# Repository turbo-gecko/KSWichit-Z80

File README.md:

# KS Wichit Z80 Microprocessor Kit

The KS Wichit Z80 Microprocessor Kit is a modern retro re-imagining of the MPF-1 microprocessor trainer. The home page for the Z80 kit is https://kswichit.net/Z80/Z80.html

After expanding my original MPF-1, I figured I could do the same for the Z80 kit. I would use the same/similar expansion bus and cards as the MPF-1, but would need a specialised adapter to connect to the Z80 kit.

This repo is for the hardware and software I have developed for the Z80 kit to expand and improve the Z80 kits useability.

## How to expand the Z80 Kit
The following section descibes how to expand the capabilities of the Z80 kit to make use conveniences like fast serial download, SD card storage etc.

The expansion bus of choice that works very well with the Z80 kit is the retro modern RCBus by Small Computer Central, and the RC2014 bus. 2 adapter cards are required to connect the Z80 kit to the expansion bus.
- Z80 kit to Z80 bus adapter. https://github.com/turbo-gecko/KSWichit-Z80/tree/main/Hardware/Z80%20Bus%20Adapter
- Z80 bus to RC2014 adapter. https://github.com/turbo-gecko/MPF/tree/main/Hardware/Z80%20Bus%20to%20RCBus

### Basic expansion bus
A basic expansion bus will require as a minimum:
- RCBus/RC2014 backplane. The one in the photo is an SC147 https://smallcomputercentral.com/sc147-modular-backplane-rc2014/
- A power supply for the backplane. The one in the photo is an SC142 that has been modified to switch the incoming 9VDC to the Z80 kit. This allows a single switch to power on/off the complete system. https://smallcomputercentral.com/sc142-power-module-rc2014/
- 40 pin ribbon cable to connect the Z80 kit to the backplane via the adapter.

This provides the necessary backplane, power and connectivity to expand the Z80 kit.

### Adding additional memory
The Z80 kit comes with 32K of RAM fitted from 1000H to 8FFFH. This is a useful amount of memory however it can be expanded to a full 60K of RAM, from 1000H to FFFFH.

First is to modify the 16V8 PAL chip to reduce the existing 32K of RAM back to 28K to allow for the second additional memory bank. The changes are included at https://github.com/turbo-gecko/KSWichit-Z80/tree/main/Hardware/16V8%20PAL

Second is a memory expansion card with 32K of RAM such as:
- The 32K RAM, standard bus version of the module at https://z80kits.com/shop/64k-ram-module/ is a good choice. This is the module that is fitted in the backplane in the photo's. It has been configured to provide RAM from 8000H through to FFFFH.

### High speed serial
The expansion bus allows a high speed serial card to be added and along with a hex download program. This enables much faster downloading of hex files to the Z80 kit compared to the onboard bit-banged serial port. The serial card in the photo's is an ACIA single serial card. https://smallcomputercentral.com/sc139-serial-68b50-module-rc2014/

### SD card storage
To store and load files using an SD card only requires an I/O card and an Adafruit style SD card adapter. The I/O card in the photo is an SC129 https://smallcomputercentral.com/sc129-digital-i-o-rc2014/.

### Optional ROM upgrade
This is an optional step to enable the faster hex file downloading from within the ROM. It is not required, as the onbaord hex loader can be used.

The ROMs at https://github.com/turbo-gecko/KSWichit-Z80/tree/main/Hardware/ROM contain the hex-load program at 0DD0H that uses the high speed serial card.

Burn the binary image to a 27C256 EPROM and replace the existing ROM the Z80 kit.

### Configuration

#### Serial
The software has been designed to work with an ACIA serial card only (more in the works) at I/O address C8H. The hex load and SD card programs are designed to use the serial card at 115kbps with RTS/CTS handshaking. There is further information on the serial card at https://github.com/turbo-gecko/MPF/tree/main/Software/Hex%20Load

#### SD Card
The I/O card should be configured to use address FDH, however this can be modified along with the pin configurations in the spi_IO.ASM file at https://github.com/turbo-gecko/MPF/tree/main/Software/Library.

Default pin configurations as follows:
| I/O | Pin | Description |
| --- | --- | ----------- |
| In  |  7  | MISO        |
| Out |  0  | MOSI        |
| Out |  1  | CLK         |
| Out |  2  | CS          |

Make sure that the SD card module is designed to run off 5VDC and has the 3V3 reg on board to drive the SD card correctly.

### Using the expansion cards
Once you have everything up and running, you can try using the hex load program at 0DD0H (if the optional ROM upgrade is done) or by pressing the 'LOAD' button to download the 'Port LED Walk' example (Port LED Walk.hex) from https://github.com/turbo-gecko/KSWichit-Z80/tree/main/Software/Examples. Download the hex file and run the program at 1800H.

### Troubleshooting
- Start with the backplane, power supply and ribbon cable first. Make sure that when both the backplane and the Z80 kit is powered on, the Z80 kit works as normal.
- Power off the system, add the expansion cards one at a time, power back on and confirm the Z80 kit is working. If it isn't check
  - The ribbon cable is connected correctly. See photo for details.
  - The expansion card is seated correctly in the backplane.

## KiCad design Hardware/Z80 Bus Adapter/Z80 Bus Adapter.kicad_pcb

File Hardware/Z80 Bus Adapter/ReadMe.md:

# Z80 Bus Adapter

Here are the files for the PCB to modify the Z80 kit expansion bus to the standard Z80 bus. The 'plots' folder contains the zip file of the grebers for a PCB manufacturer house such as JLCPCB.

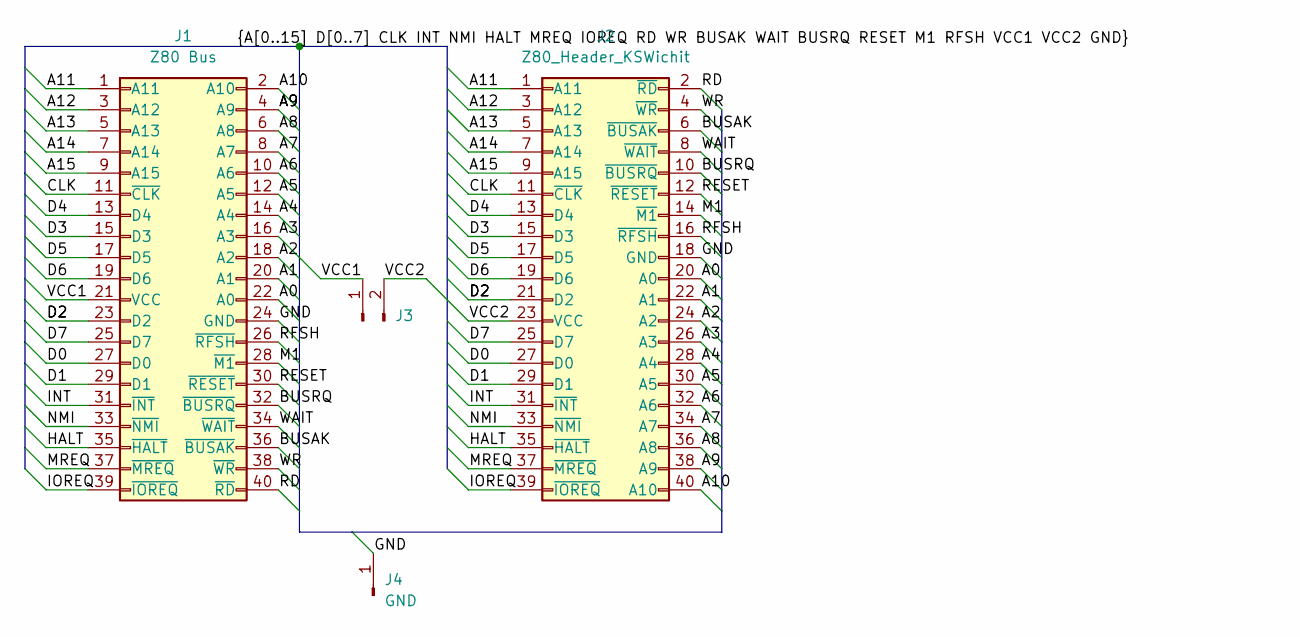
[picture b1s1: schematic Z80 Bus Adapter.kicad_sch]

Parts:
J1: Z80 Bus; PinSocket_2x20_P2.54mm_Vertical
J2: Z80_Header_KSWichit; PinSocket_2x20_P2.54mm_Vertical
J3: Conn_01x02_Pin; PinHeader_1x02_P2.54mm_Vertical
J4: GND; PinHeader_1x01_P2.54mm_Vertical

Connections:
/A0: J1.22 (A0), J2.20 (A0)
/A1: J1.20 (A1), J2.22 (A1)
/A2: J1.18 (A2), J2.24 (A2)
/A3: J1.16 (A3), J2.26 (A3)
/A4: J1.14 (A4), J2.28 (A4)
/A5: J1.12 (A5), J2.30 (A5)
/A6: J1.10 (A6), J2.32 (A6)
/A7: J1.8 (A7), J2.34 (A7)
/A8: J1.6 (A8), J2.36 (A8)
/A9: J1.4 (A9), J2.38 (A9)
/A10: J1.2 (A10), J2.40 (A10)
/A11: J1.1 (A11), J2.1 (A11)
/A12: J1.3 (A12), J2.3 (A12)
/A13: J1.5 (A13), J2.5 (A13)
/A14: J1.7 (A14), J2.7 (A14)
/A15: J1.9 (A15), J2.9 (A15)
/BUSAK: J1.36 (~BUSAK), J2.6 (~BUSAK)
/BUSRQ: J1.32 (~BUSRQ), J2.10 (~BUSRQ)
/CLK: J1.11 (~CLK), J2.11 (~CLK)
/D0: J1.27 (D0), J2.27 (D0)
/D1: J1.29 (D1), J2.29 (D1)
/D2: J1.23 (D2), J2.21 (D2)
/D3: J1.15 (D3), J2.15 (D3)
/D4: J1.13 (D4), J2.13 (D4)
/D5: J1.17 (D5), J2.17 (D5)
/D6: J1.19 (D6), J2.19 (D6)
/D7: J1.25 (D7), J2.25 (D7)
/GND: J1.24 (GND), J2.18 (GND), J4.1
/HALT: J1.35 (~HALT), J2.35 (~HALT)
/INT: J1.31 (~INT), J2.31 (~INT)
/IOREQ: J1.39 (~IOREQ), J2.39 (~IOREQ)
/M1: J1.28 (~M1), J2.14 (~M1)
/MREQ: J1.37 (~MREQ), J2.37 (~MREQ)
/NMI: J1.33 (~NMI), J2.33 (~NMI)
/RD: J1.40 (~RD), J2.2 (~RD)
/RESET: J1.30 (~RESET), J2.12 (~RESET)
/RFSH: J1.26 (~RFSH), J2.16 (~RFSH)
/VCC1: J1.21 (VCC), J3.1
/VCC2: J2.23 (VCC), J3.2
/WAIT: J1.34 (~WAIT), J2.8 (~WAIT)
/WR: J1.38 (~WR), J2.4 (~WR)

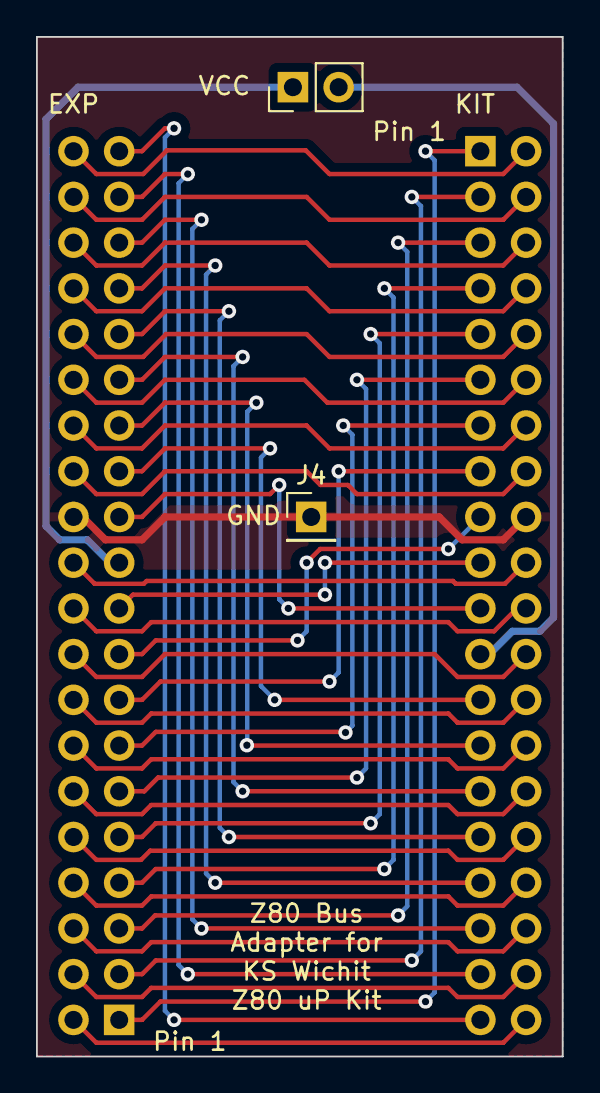
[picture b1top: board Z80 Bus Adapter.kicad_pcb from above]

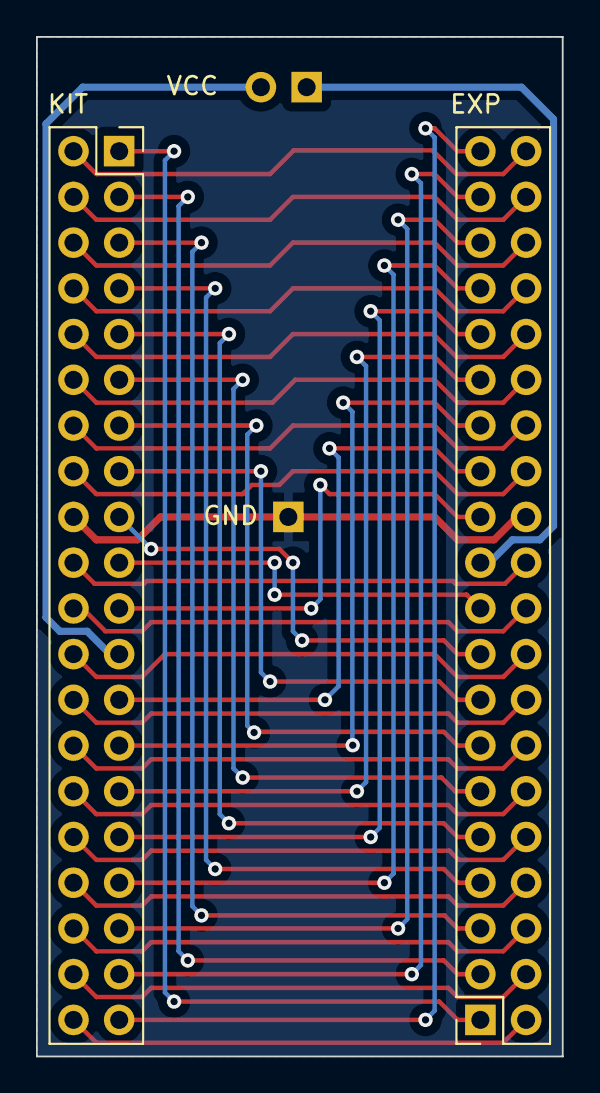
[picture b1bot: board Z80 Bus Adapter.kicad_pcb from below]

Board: 2 copper layers, 29.2 x 56.6 mm, 4 parts (2 on the bottom side), 41 nets.

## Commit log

2024-08-13 Added photo's
2024-08-13 3D Print Files
2024-08-14 Z80 Bus Adapter
2024-08-14 16V8 PAL Changes
2024-08-14 Added example programs
2024-08-14 Updated ROM folder
2024-08-14 Workbook examples update
2024-08-14 New ROM added
2024-08-15 Added original ROM image
2024-08-15 Added .lst files
2024-08-16 MPF-1 Option ROM addressing
2024-08-16 Updated examples
2024-08-16 Updated PAL 16V8
